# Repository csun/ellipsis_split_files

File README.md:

KiCad files for the pcb in the `pcb/` directory

dxf files for the plates in the `plates/` directory. This includes files for the templates used to cut out the wrist rests.

# V2 Construction Notes

The board is laid out for [this specific aliexpress promicro clone](https://www.aliexpress.us/item/2251801162485383.html?spm=a2g0o.order_list.order_list_main.5.74b51802ReslBv&gatewayAdapt=glo2usa&_randl_shipto=US). You can probably use a standard promicro, but the USB port will not be flush with the edge of the board.

The toggle switch used is the [E-Switch 100SP1T2B4M6QE](https://www.digikey.com/en/products/detail/e-switch/100SP1T2B4M6QE/378831?utm_medium=email&utm_source=oce&utm_campaign=4251_OCE22RT&utm_content=productdetail_US&utm_cid=3431001&so=79302515&mkt_tok=MDI4LVNYSy01MDcAAAGI5V8zllvVve2cTX5U4Xojm0RMn3Iq-sOntSVT2qtzfiGTsQoptobogo4Q5rgp82cGebamFCV9cWvPupQOrgY6sCrZjn-3Wv1uY3PDjv02). TBH I'd buy a clone of this off aliexpress too and save yourself a bunch of money.

Firmware source can be found [here](https://github.com/csun/qmk_firmware/tree/ellipsis_split_v2) on the `ellipsis_split_v2` branch.

# V1 Construction Notes

Most of the components needed for assembly should be properly labelled in the pcb files. The screen used is [this adafruit one](https://www.adafruit.com/product/931) based on the SSD1306 driver chip.

I cut wrist rests from wood using the router template included in the plates directory.

You'll also need M2 standoffs of various lengths to separate the two plates enough to fit the PCB. I think around 12mm is the minimum allowable height.

Firmware source uses QMK and can be found [here](https://github.com/csun/ellipsis_split_firmware)

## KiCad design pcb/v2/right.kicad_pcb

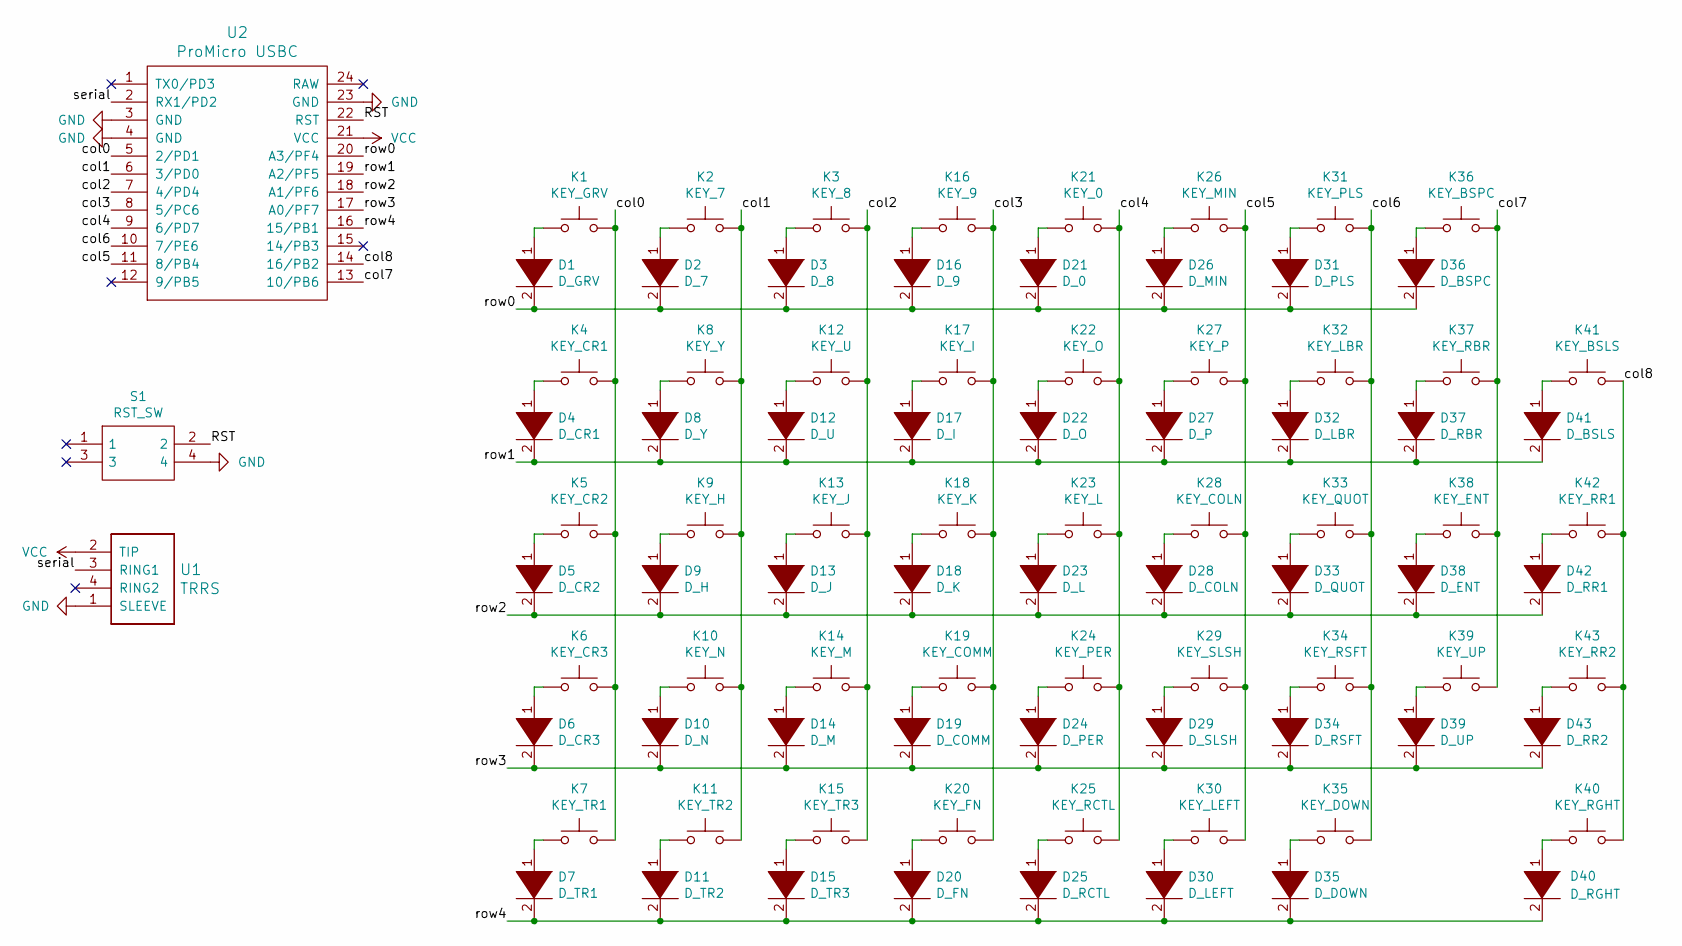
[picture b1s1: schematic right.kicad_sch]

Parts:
D1: D_GRV; D_SOD123_axial
D2: D_7; D_SOD123_axial
D3: D_8; D_SOD123_axial
D4: D_CR1; D_SOD123_axial
D5: D_CR2; D_SOD123_axial
D6: D_CR3; D_SOD123_axial
D7: D_TR1; D_SOD123_axial
D8: D_Y; D_SOD123_axial
D9: D_H; D_SOD123_axial
D10: D_N; D_SOD123_axial
D11: D_TR2; D_SOD123_axial
D12: D_U; D_SOD123_axial
D13: D_J; D_SOD123_axial
D14: D_M; D_SOD123_axial
D15: D_TR3; D_SOD123_axial
D16: D_9; D_SOD123_axial
D17: D_I; D_SOD123_axial
D18: D_K; D_SOD123_axial
D19: D_COMM; D_SOD123_axial
D20: D_FN; D_SOD123_axial
D21: D_0; D_SOD123_axial
D22: D_O; D_SOD123_axial
D23: D_L; D_SOD123_axial
D24: D_PER; D_SOD123_axial
D25: D_RCTL; D_SOD123_axial
D26: D_MIN; D_SOD123_axial
D27: D_P; D_SOD123_axial
D28: D_COLN; D_SOD123_axial
D29: D_SLSH; D_SOD123_axial
D30: D_LEFT; D_SOD123_axial
D31: D_PLS; D_SOD123_axial
D32: D_LBR; D_SOD123_axial
D33: D_QUOT; D_SOD123_axial
D34: D_RSFT; D_SOD123_axial
D35: D_DOWN; D_SOD123_axial
D36: D_BSPC; D_SOD123_axial
D37: D_RBR; D_SOD123_axial
D38: D_ENT; D_SOD123_axial
D39: D_UP; D_SOD123_axial
D40: D_RGHT; D_SOD123_axial
D41: D_BSLS; D_SOD123_axial
D42: D_RR1; D_SOD123_axial
D43: D_RR2; D_SOD123_axial
K1: KEY_GRV; Mx_Alps_100
K2: KEY_7; Mx_Alps_100
K3: KEY_8; Mx_Alps_100
K4: KEY_CR1; Mx_Alps_100
K5: KEY_CR2; Mx_Alps_100
K6: KEY_CR3; Mx_Alps_100
K7: KEY_TR1; Mx_Alps_100
K8: KEY_Y; Mx_Alps_100
K9: KEY_H; Mx_Alps_100
K10: KEY_N; Mx_Alps_100
K11: KEY_TR2; Mx_Alps_125
K12: KEY_U; Mx_Alps_100
K13: KEY_J; Mx_Alps_100
K14: KEY_M; Mx_Alps_100
K15: KEY_TR3; Mx_Alps_125
K16: KEY_9; Mx_Alps_100
K17: KEY_I; Mx_Alps_100
K18: KEY_K; Mx_Alps_100
K19: KEY_COMM; Mx_Alps_100
K20: KEY_FN; Mx_Alps_125
K21: KEY_0; Mx_Alps_100
K22: KEY_O; Mx_Alps_100
K23: KEY_L; Mx_Alps_100
K24: KEY_PER; Mx_Alps_100
K25: KEY_RCTL; Mx_Alps_125
K26: KEY_MIN; Mx_Alps_100
K27: KEY_P; Mx_Alps_100
K28: KEY_COLN; Mx_Alps_100
K29: KEY_SLSH; Mx_Alps_100
K30: KEY_LEFT; Mx_Alps_100
K31: KEY_PLS; Mx_Alps_100
K32: KEY_LBR; Mx_Alps_100
K33: KEY_QUOT; Mx_Alps_100
K34: KEY_RSFT; Mx_Alps_125
K35: KEY_DOWN; Mx_Alps_100
K36: KEY_BSPC; Mx_Alps_150
K37: KEY_RBR; Mx_Alps_100
K38: KEY_ENT; Mx_Alps_175
K39: KEY_UP; Mx_Alps_100
K40: KEY_RGHT; Mx_Alps_100
K41: KEY_BSLS; Mx_Alps_100
K42: KEY_RR1; Mx_Alps_100
K43: KEY_RR2; Mx_Alps_100
S1: RST_SW; LL3301NF065QG; Mouser Part Number 612-LL3301NF065QG
U1: TRRS; TRRS-PJ-320A
U2: ProMicro USBC; ArduinoProMicro-USBC-Alibaba

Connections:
/RST: S1.2, U2.22 (RST)
/col0: K1.2, K4.2, K5.2, K6.2, K7.2, U2.5 (2/PD1)
/col1: K2.2, K8.2, K9.2, K10.2, K11.2, U2.6 (3/PD0)
/col2: K3.2, K12.2, K13.2, K14.2, K15.2, U2.7 (4/PD4)
/col3: K16.2, K17.2, K18.2, K19.2, K20.2, U2.8 (5/PC6)
/col4: K21.2, K22.2, K23.2, K24.2, K25.2, U2.9 (6/PD7)
/col5: K26.2, K27.2, K28.2, K29.2, K30.2, U2.11 (8/PB4)
/col6: K31.2, K32.2, K33.2, K34.2, K35.2, U2.10 (7/PE6)
/col7: K36.2, K37.2, K38.2, K39.2, U2.13 (10/PB6)
/col8: K40.2, K41.2, K42.2, K43.2, U2.14 (16/PB2)
/row0: D1.2 (A), D2.2 (A), D3.2 (A), D16.2 (A), D21.2 (A), D26.2 (A), D31.2 (A), D36.2 (A), U2.20 (A3/PF4)
/row1: D4.2 (A), D8.2 (A), D12.2 (A), D17.2 (A), D22.2 (A), D27.2 (A), D32.2 (A), D37.2 (A), D41.2 (A), U2.19 (A2/PF5)
/row2: D5.2 (A), D9.2 (A), D13.2 (A), D18.2 (A), D23.2 (A), D28.2 (A), D33.2 (A), D38.2 (A), D42.2 (A), U2.18 (A1/PF6)
/row3: D6.2 (A), D10.2 (A), D14.2 (A), D19.2 (A), D24.2 (A), D29.2 (A), D34.2 (A), D39.2 (A), D43.2 (A), U2.17 (A0/PF7)
/row4: D7.2 (A), D11.2 (A), D15.2 (A), D20.2 (A), D25.2 (A), D30.2 (A), D35.2 (A), D40.2 (A), U2.16 (15/PB1)
/serial: U1.3 (RING1), U2.2 (RX1/PD2)
GND: S1.4, U1.1 (SLEEVE), U2.3 (GND), U2.4 (GND), U2.23 (GND)
unnamed: D1.1 (K), K1.1
unnamed: D2.1 (K), K2.1
unnamed: D3.1 (K), K3.1
unnamed: D4.1 (K), K4.1
unnamed: D5.1 (K), K5.1
unnamed: D6.1 (K), K6.1
unnamed: D7.1 (K), K7.1
unnamed: D8.1 (K), K8.1
unnamed: D9.1 (K), K9.1
unnamed: D10.1 (K), K10.1
unnamed: D11.1 (K), K11.1
unnamed: D12.1 (K), K12.1
unnamed: D13.1 (K), K13.1
unnamed: D14.1 (K), K14.1
unnamed: D15.1 (K), K15.1
unnamed: D16.1 (K), K16.1
unnamed: D17.1 (K), K17.1
unnamed: D18.1 (K), K18.1
unnamed: D19.1 (K), K19.1
unnamed: D20.1 (K), K20.1
unnamed: D21.1 (K), K21.1
unnamed: D22.1 (K), K22.1
unnamed: D23.1 (K), K23.1
unnamed: D24.1 (K), K24.1
unnamed: D25.1 (K), K25.1
unnamed: D26.1 (K), K26.1
unnamed: D27.1 (K), K27.1
unnamed: D28.1 (K), K28.1
unnamed: D29.1 (K), K29.1
unnamed: D30.1 (K), K30.1
unnamed: D31.1 (K), K31.1
unnamed: D32.1 (K), K32.1
unnamed: D33.1 (K), K33.1
unnamed: D34.1 (K), K34.1
unnamed: D35.1 (K), K35.1
unnamed: D36.1 (K), K36.1
unnamed: D37.1 (K), K37.1
unnamed: D38.1 (K), K38.1
unnamed: D39.1 (K), K39.1
unnamed: D41.1 (K), K41.1
unnamed: D42.1 (K), K42.1
unnamed: D43.1 (K), K43.1
unnamed: D40.1 (K), K40.1
VCC: U1.2 (TIP), U2.21 (VCC)

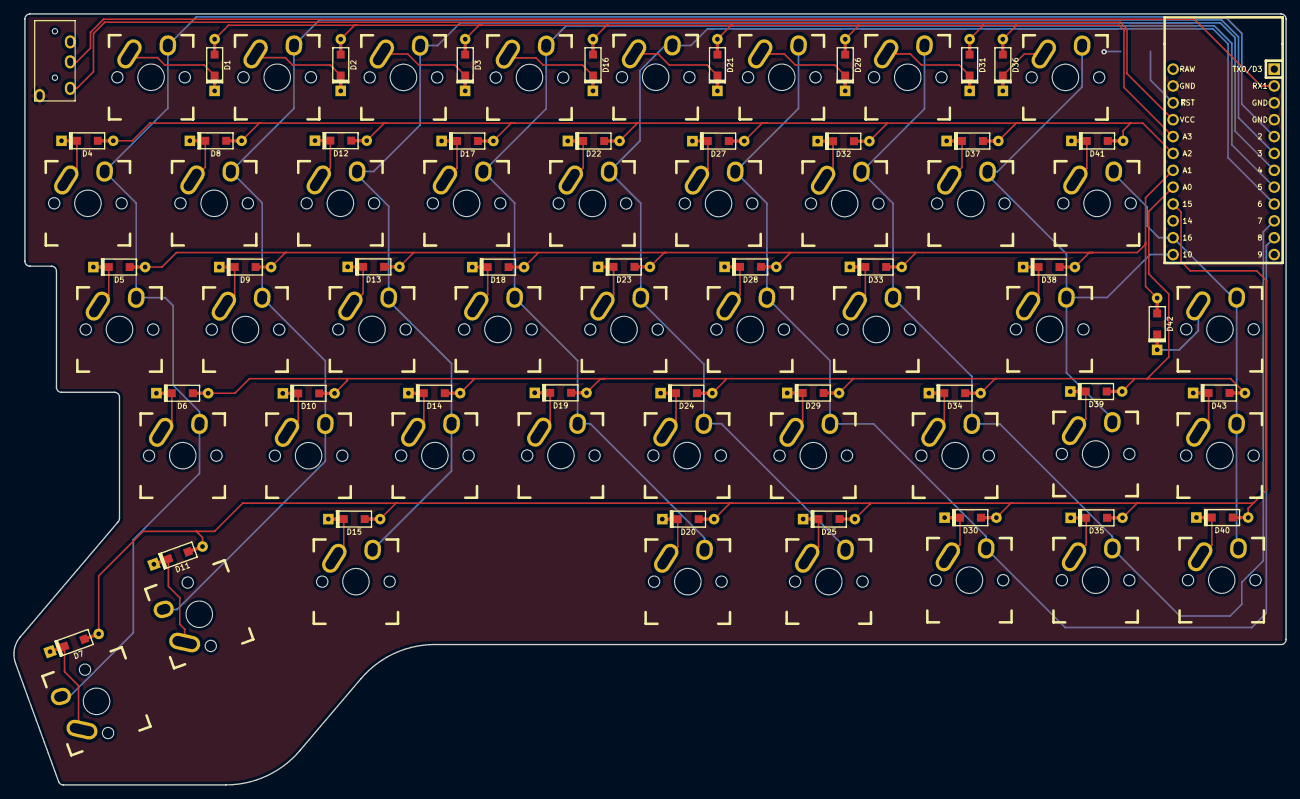
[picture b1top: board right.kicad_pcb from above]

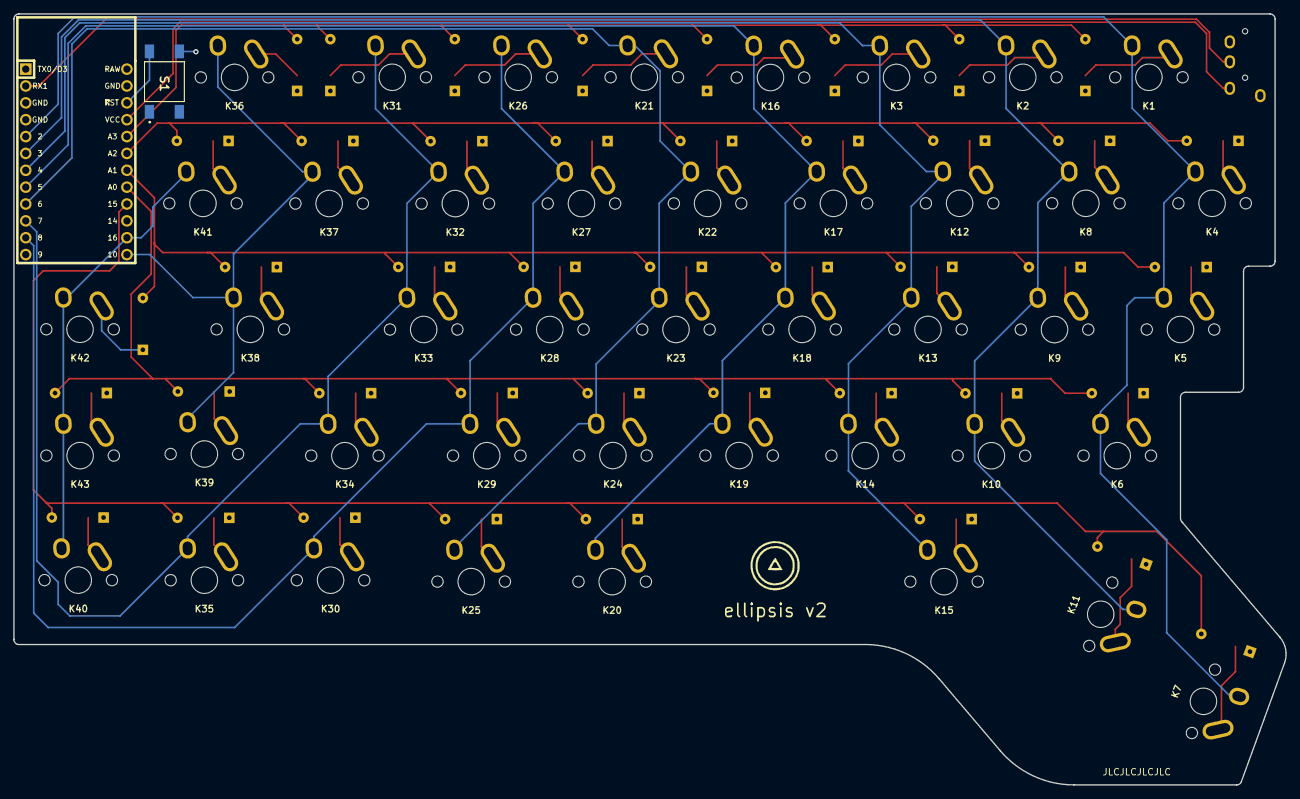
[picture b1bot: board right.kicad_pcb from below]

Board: 2 copper layers, 191.7 x 116.2 mm, 89 parts (2 on the bottom side), 61 nets.

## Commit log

2020-09-23 Initial
2022-12-21 start work on v2
2022-12-24 Starting to wire left side
2022-12-24 Left pcb should be done
2022-12-24 Starting on right pcb
2022-12-26 Trying to add some fillets but something is messed up
2022-12-26 Whatever
2022-12-27 This is the version that I sent to manufacturers
2022-12-27 Reorganized so that pcb has v1 and v2 folders too
